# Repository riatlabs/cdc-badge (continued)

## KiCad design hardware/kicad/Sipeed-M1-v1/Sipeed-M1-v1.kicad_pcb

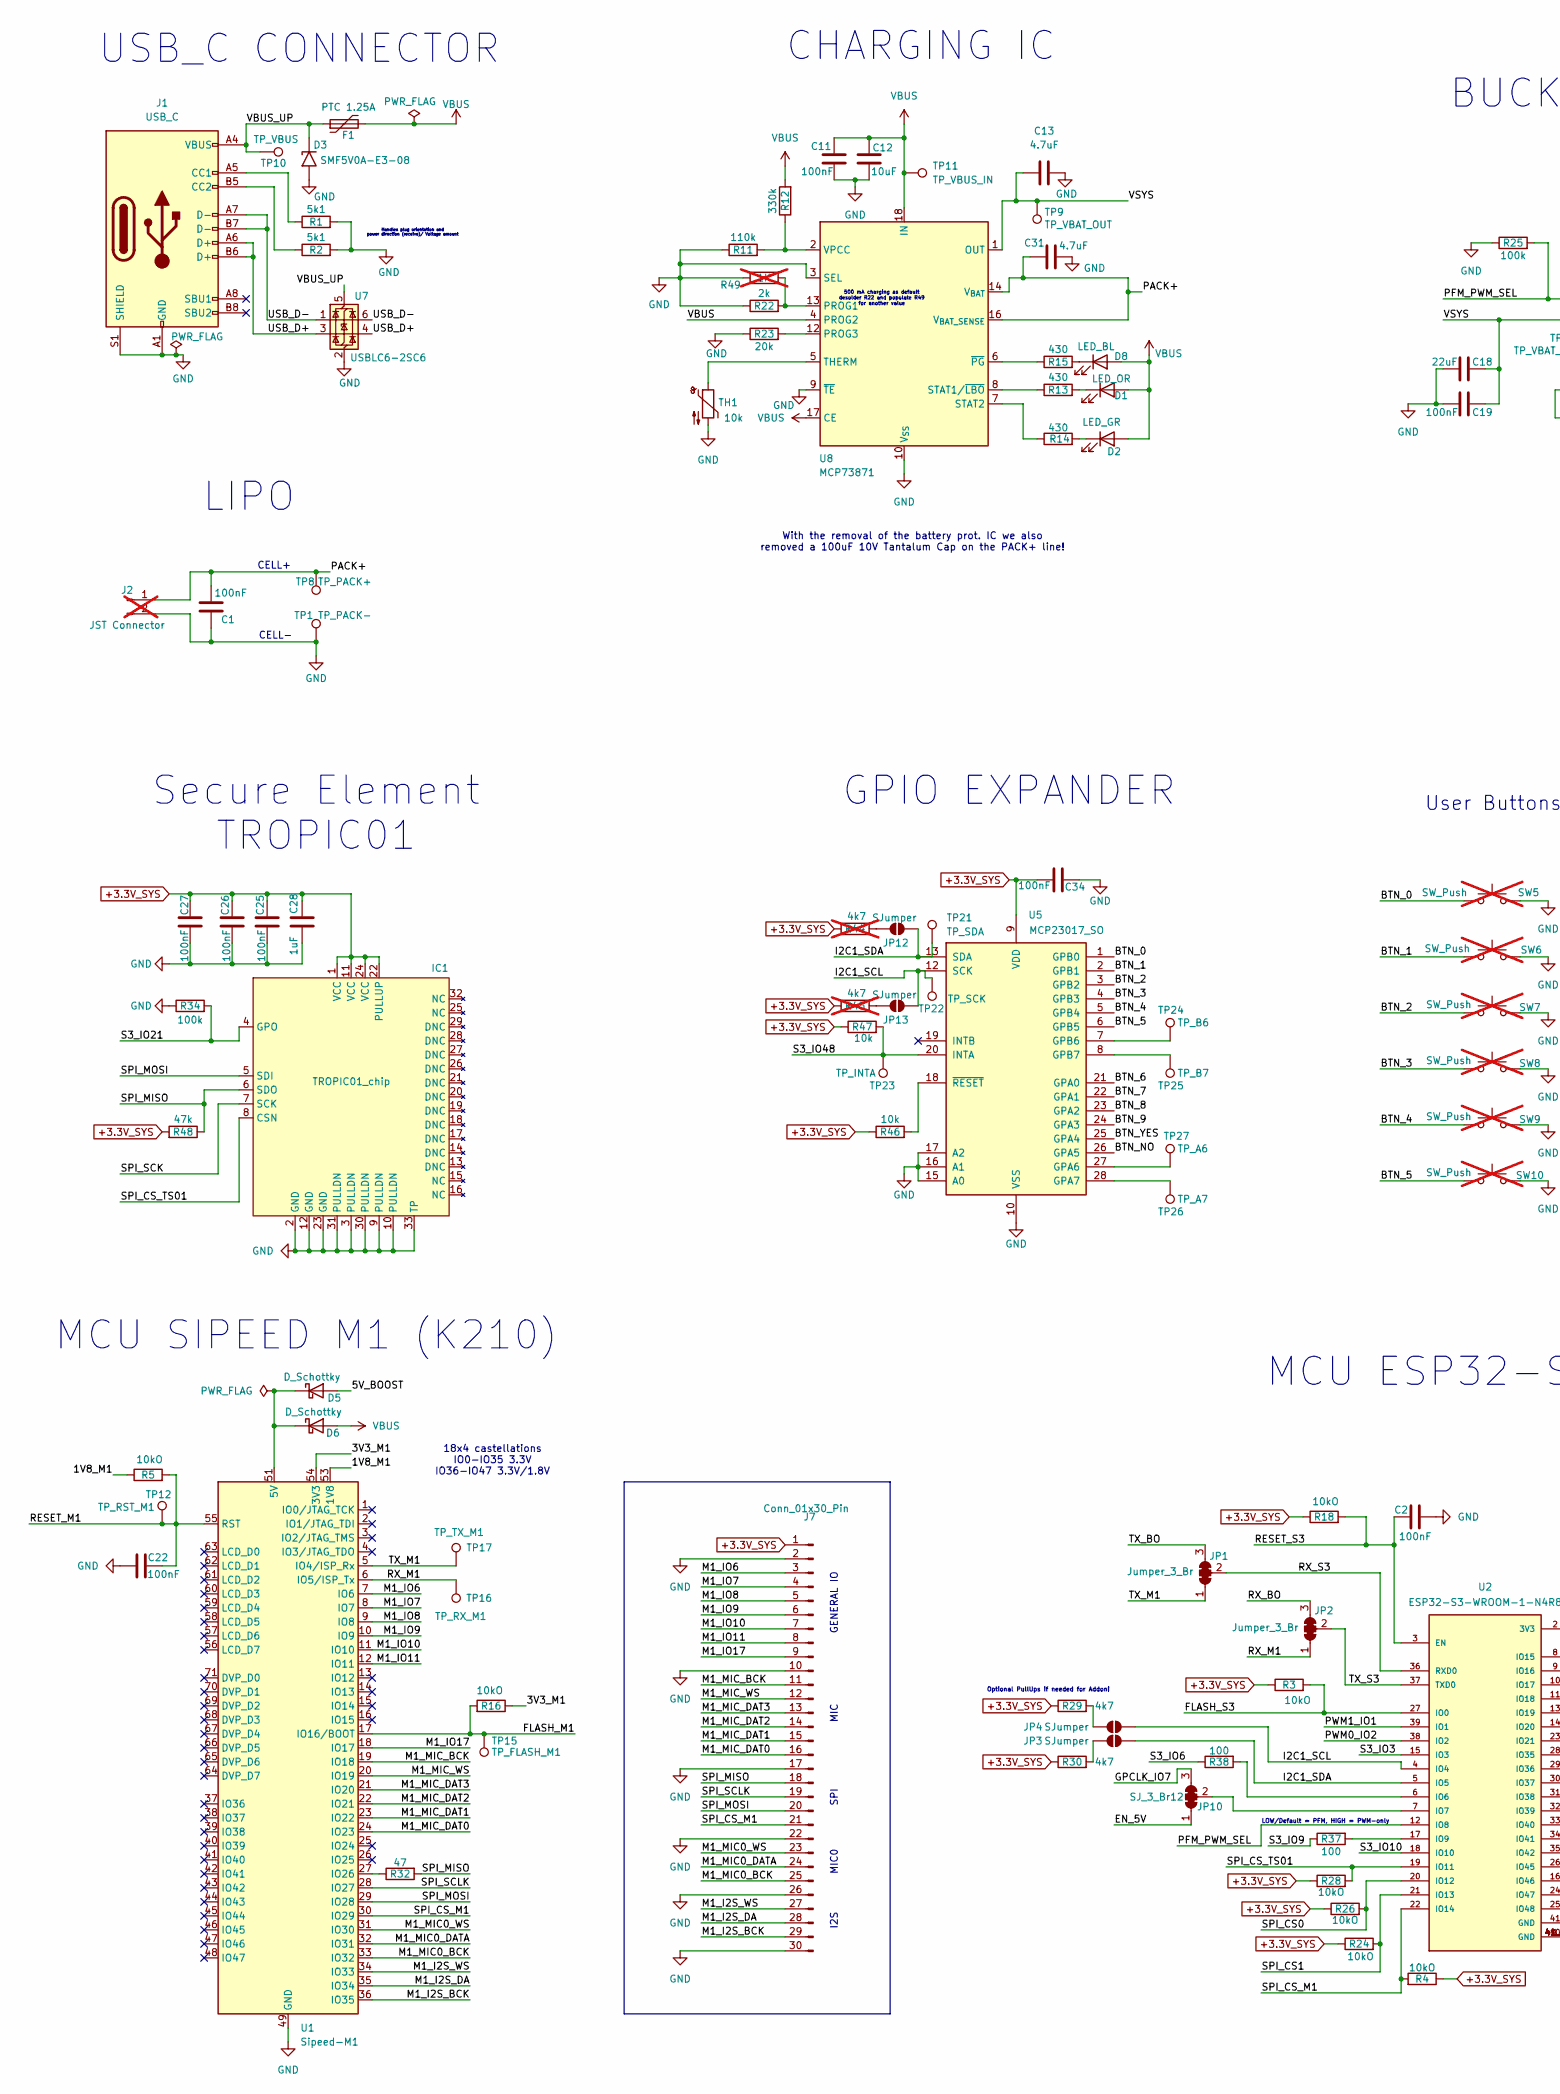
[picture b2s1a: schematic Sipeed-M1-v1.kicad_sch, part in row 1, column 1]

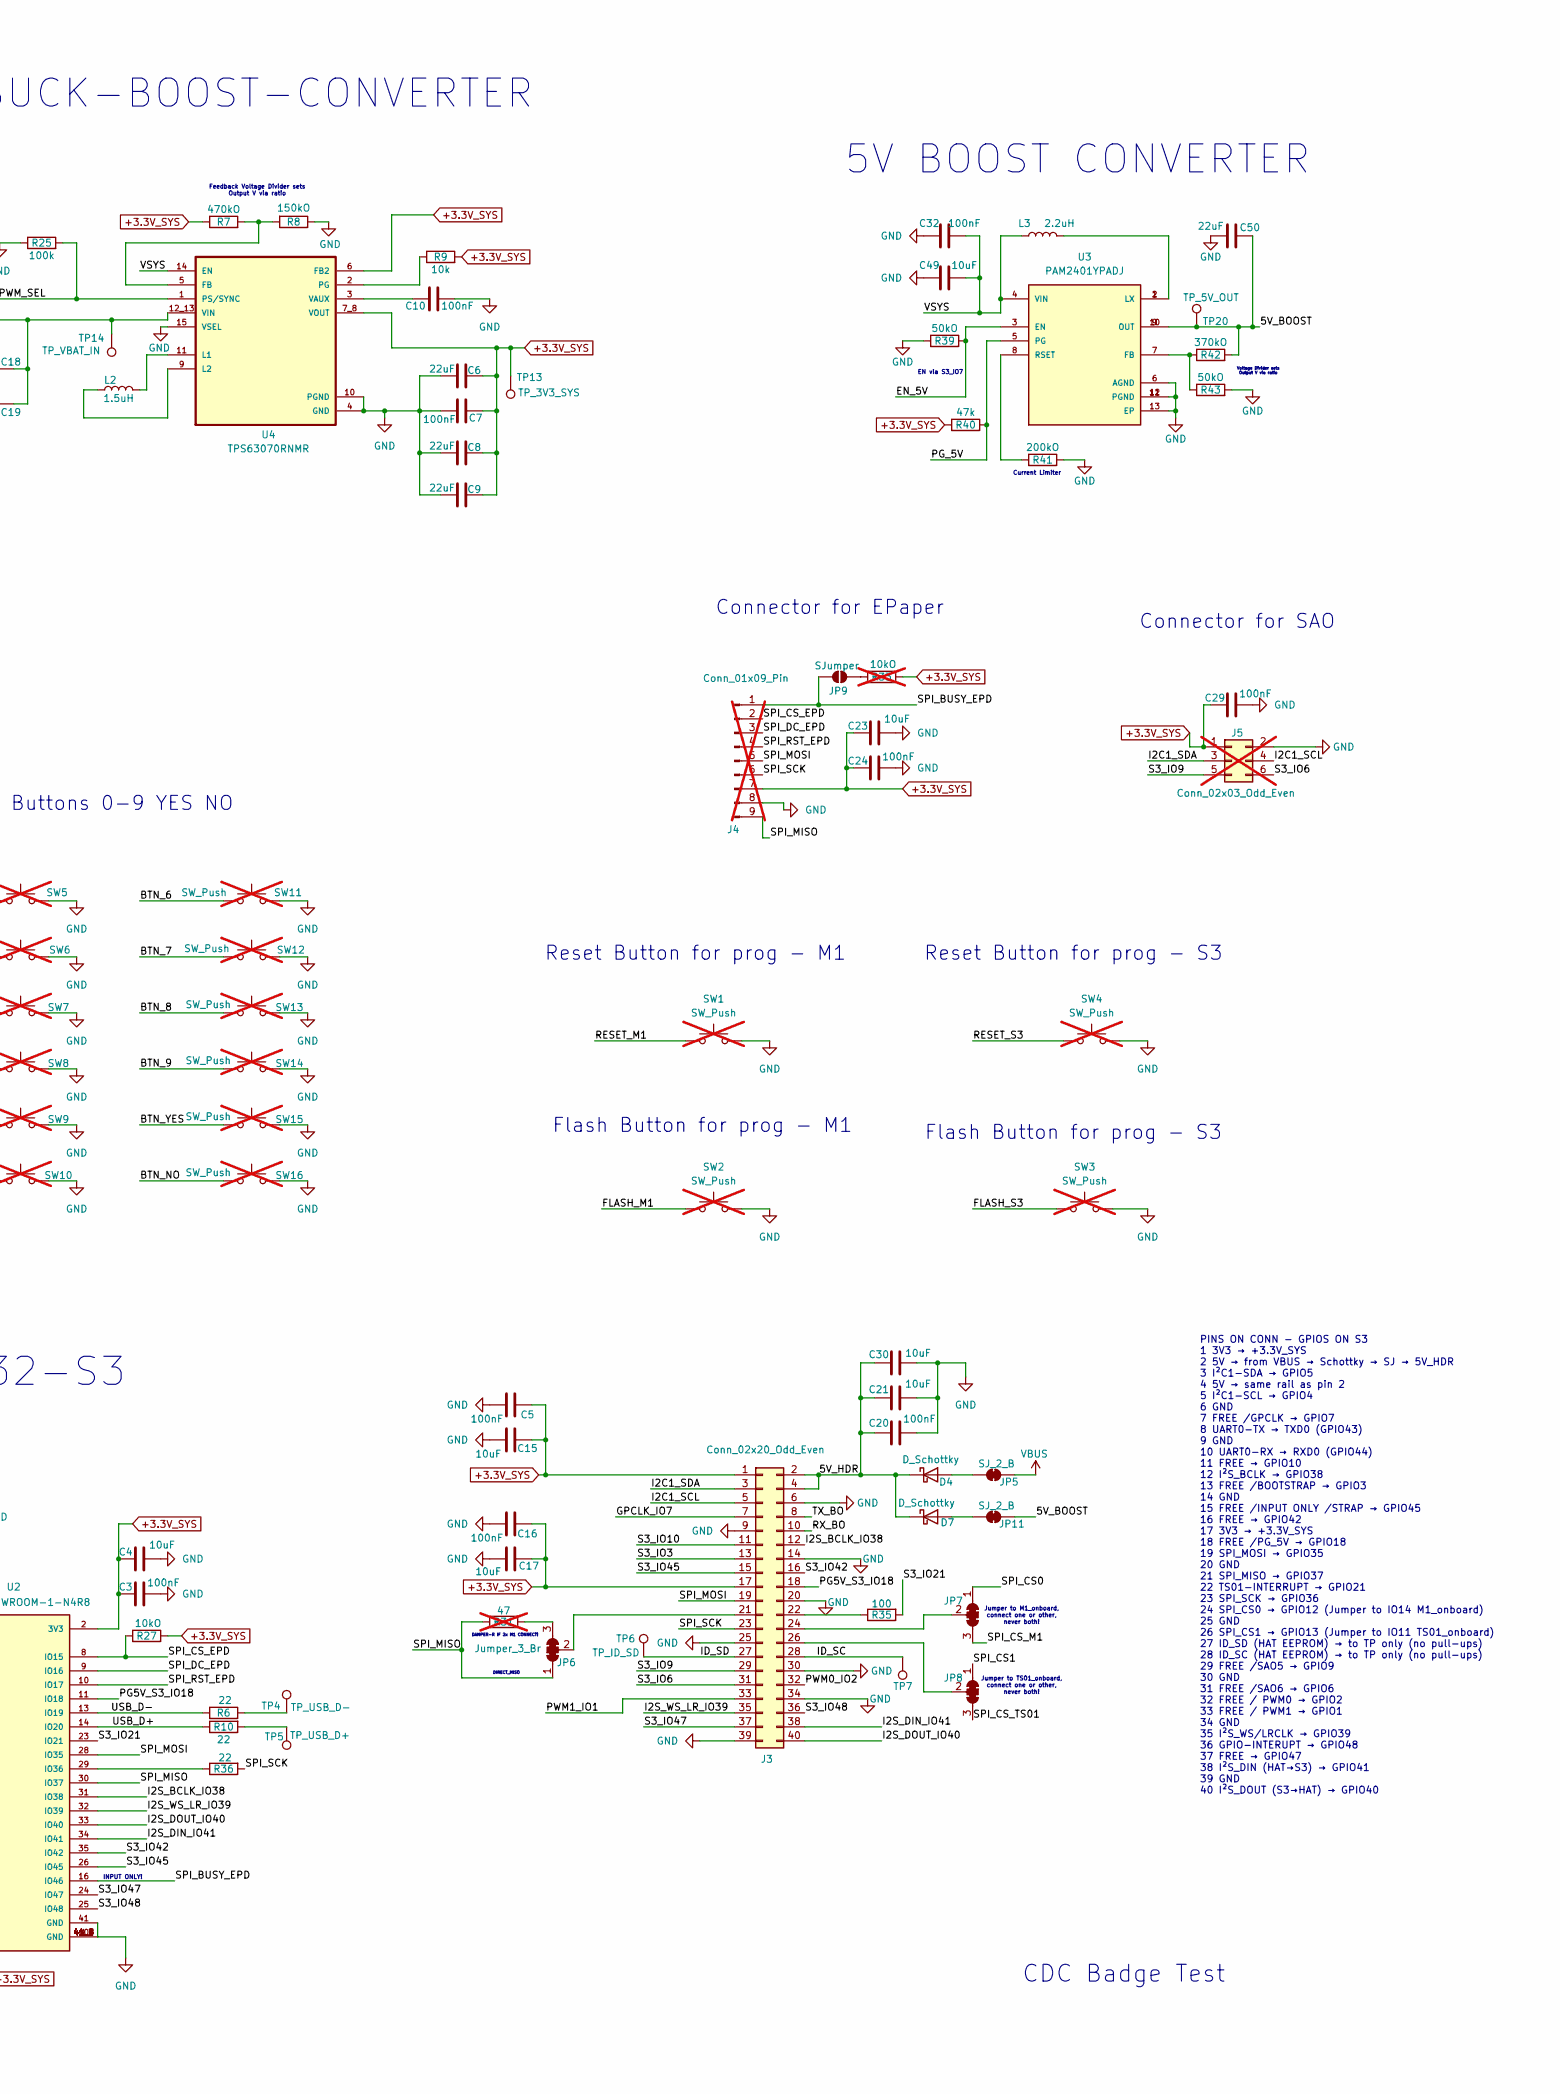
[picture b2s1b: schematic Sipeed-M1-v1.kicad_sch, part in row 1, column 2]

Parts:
C1, C2, C3, C5, C7, C10, C11, C16, C19, C20, C22, C24, C25, C26, C27, C29, C34: 100nF; C_0603_1608Metric
C4, C12, C15, C17, C21, C23, C30: 10uF; C_1206_3216Metric
C6, C8, C9, C18: 22uF; C_1206_3216Metric
C13, C31: 4.7uF; C_1206_3216Metric
C28: 1uF; C_0805_2012Metric
C32: 100nF; CP_EIA-3528-12_Kemet-T
C49: 10uF; CP_EIA-3528-12_Kemet-T
C50: 22uF; CP_EIA-3528-12_Kemet-T
D1: LED_OR; LED_0603_1608Metric
D2: LED_GR; LED_0603_1608Metric
D3: SMF5V0A-E3-08; D_SMF; JLCPCB PN C1972946
D4, D5, D6, D7: D_Schottky; D_SOD-123F
D8: LED_BL; LED_0603_1608Metric
F1: PTC 1.25A; Fuse_1812_4532Metric
IC1: TROPIC01_chip; TROPIC_QFN-32-1EP_4x4mm_P0.4mm_EP2.65x2.65mm
J1: USB_C; SHOUHAN_TYPE-C_16PIN_2MD__073_; JLCPCB PN C2765186
J2: JST Connector; JST_PH_S2B-PH-SM4-TB_1x02-1MP_P2.00mm_Horizontal; not fitted
J3: Conn_02x20_Odd_Even; PinHeader_2x20_P2.54mm_Vertical
J4: Conn_01x09_Pin; PinHeader_1x09_P2.54mm_Vertical; not fitted
J5: Conn_02x03_Odd_Even; PinSocket_2x03_P2.54mm_Vertical; not fitted
J7: Conn_01x30_Pin; PinHeader_1x30_P2.54mm_Vertical
JP1, JP2, JP6: Jumper_3_Br; SolderJumper-3_P1.3mm_Bridged12_RoundedPad1.0x1.5mm_NumberL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
JP3, JP4: SJumper; SolderJumper-2_P1.3mm_Bridged_RoundedPad1.0x1.5mm
JP5, JP11: SJ_2_B; SolderJumper-2_P1.3mm_Bridged_RoundedPad1.0x1.5mm
JP7, JP8: Jump_3_Br12; SolderJumper-3_P1.3mm_Bridged12_RoundedPad1.0x1.5mm_NumberL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
JP9, JP12, JP13: SJumper; SolderJumper-2_P1.3mm_Open_RoundedPad1.0x1.5mm
JP10: SJ_3_Br12; SolderJumper-3_P1.3mm_Bridged12_RoundedPad1.0x1.5mm_NumberL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
L2: 1.5uH; L_6.3x6.3_H3
L3: 2.2uH; L_6.3x6.3_H3
R1, R2: 5k1; R_0402_1005Metric
R3, R4, R5, R16, R18, R24, R26, R27, R28: 10kO; R_0603_1608Metric
R6, R10, R36: 22; R_0603_1608Metric
R7: 470kO; R_0805_2012Metric
R8: 150kO; R_0805_2012Metric
R9, R46, R47: 10k; R_0603_1608Metric
R11: 110k; R_0805_2012Metric
R12: 330k; R_0805_2012Metric
R13, R14, R15: 430; R_0603_1608Metric
R22: 2k; R_0603_1608Metric
R23: 20k; R_0603_1608Metric
R25: 100k; R_0805_2012Metric
R29, R30: 4k7; R_0603_1608Metric
R31: 47; R_Axial_DIN0207_L6.3mm_D2.5mm_P7.62mm_Horizontal; not fitted
R32: 47; R_0603_1608Metric
R33: 10kO; R_Axial_DIN0207_L6.3mm_D2.5mm_P7.62mm_Horizontal; not fitted
R34: 100k; R_0603_1608Metric
R35, R37, R38: 100; R_0603_1608Metric
R39, R43: 50kO; R_0603_1608Metric
R40, R48: 47k; R_0603_1608Metric
R41: 200kO; R_0805_2012Metric
R42: 370kO; R_0805_2012Metric
R44, R45: 4k7; R_Axial_DIN0207_L6.3mm_D2.5mm_P7.62mm_Horizontal; not fitted
R49: 1K; R_Axial_DIN0207_L6.3mm_D2.5mm_P7.62mm_Horizontal; not fitted
SW1, SW2, SW3, SW4, SW5, SW6, SW7, SW8, SW9, SW10, SW11, SW12, SW13, SW14, SW15, SW16: SW_Push; SW_PUSH_6mm_H5mm; not fitted
TH1: 10k; Fuse_1812_4532Metric
TP1: TP_PACK-; TestPoint_Pad_D2.0mm
TP4: TP_USB_D-; TestPoint_Pad_D2.0mm
TP5: TP_USB_D+; TestPoint_Pad_D2.0mm
TP6: TP_ID_SD; TestPoint_Pad_D2.0mm
TP7: TP_ID_SC; TestPoint_Pad_D2.0mm
TP8: TP_PACK+; TestPoint_Pad_D2.0mm
TP9: TP_VBAT_OUT; TestPoint_Pad_D2.0mm
TP10: TP_VBUS; TestPoint_Pad_D2.0mm
TP11: TP_VBUS_IN; TestPoint_Pad_D2.0mm
TP12: TP_RST_M1; TestPoint_Pad_D2.0mm
TP13: TP_3V3_SYS; TestPoint_Pad_D2.0mm
TP14: TP_VBAT_IN; TestPoint_Pad_D2.0mm
TP15: TP_FLASH_M1; TestPoint_Pad_D2.0mm
TP16: TP_RX_M1; TestPoint_Pad_D2.0mm
TP17: TP_TX_M1; TestPoint_Pad_D2.0mm
TP20: TP_5V_OUT; TestPoint_Pad_D2.0mm
TP21: TP_SDA; TestPoint_Pad_D2.0mm
TP22: TP_SCK; TestPoint_Pad_D2.0mm
TP23: TP_INTA; TestPoint_Pad_D2.0mm
TP24: TP_B6; TestPoint_Pad_D2.0mm
TP25: TP_B7; TestPoint_Pad_D2.0mm
TP26: TP_A7; TestPoint_Pad_D2.0mm
TP27: TP_A6; TestPoint_Pad_D2.0mm
U1: Sipeed-M1
U2: ESP32-S3-WROOM-1-N4R8; ESP32-S3-WROOM-1; PARTREV v1.1
U3: PAM2401YPADJ; PAM2401_SON45P300X300X63-13N; PARTREV 1-2
U4: TPS63070RNMR
U5: MCP23017_SO; SOIC-28W_7.5x17.9mm_P1.27mm
U7: USBLC6-2SC6; SOT-23-6; JLCPCB PN C7519
U8: MCP73871; QFN-20-1EP_4x4mm_P0.5mm_EP2.5x2.5mm

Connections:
+3.3V_SYS: C3.1, C4.1, C5.1, C6.2, C7.2, C8.2, C9.2, C15.1, C16.1, C17.1, C23.1, C24.1, C25.1, C26.1, C27.1, C28.1, C29.1, C34.2, IC1.1 (VCC), IC1.11 (VCC), IC1.22 (PULLUP), IC1.24 (VCC), J3.1, J3.17, J4.7, J5.1, J7.1, R3.1, R4.1, R7.1, R9.2, R18.1, R24.1, R26.1, R27.1, R28.1, R29.1, R30.1, R33.1, R40.2, R44.1, R45.1, R46.1, R47.1, R48.2, TP13.1, U2.2 (3V3), U4.6 (FB2), U4.7_8 (VOUT), U5.9 (VDD)
/1V8_M1: R5.1, U1.53 (1V8)
/3V3_M1: R16.1, U1.54 (3V3)
/5V_BOOST: C50.1, D5.2 (A), JP11.2 (B), R42.2, TP20.1, U3.9 (OUT), U3.10 (OUT)
/5V_HDR: C20.1, C21.1, C30.1, D4.1 (K), D7.1 (K), J3.2, J3.4
/BTN_0: SW5.1, U5.1 (GPB0)
/BTN_1: SW6.1, U5.2 (GPB1)
/BTN_2: SW7.1, U5.3 (GPB2)
/BTN_3: SW8.1, U5.4 (GPB3)
/BTN_4: SW9.1, U5.5 (GPB4)
/BTN_5: SW10.1, U5.6 (GPB5)
/BTN_6: SW11.1, U5.21 (GPA0)
/BTN_7: SW12.1, U5.22 (GPA1)
/BTN_8: SW13.1, U5.23 (GPA2)
/BTN_9: SW14.1, U5.24 (GPA3)
/BTN_NO: SW16.1, U5.26 (GPA5)
/BTN_YES: SW15.1, U5.25 (GPA4)
/EN_5V: JP10.1 (A), R39.1, U3.3 (EN)
/FLASH_M1: R16.2, SW2.1, TP15.1, U1.17 (IO16/BOOT)
/FLASH_S3: R3.2, SW3.1, U2.27 (IO0)
/GPCLK_IO7: J3.7, JP10.3 (B)
/I2C1_SCL: J3.5, J5.4, JP4.2 (B), JP13.2 (B), TP22.1, U2.4 (IO4), U5.12 (SCK)
/I2C1_SDA: J3.3, J5.3, JP3.2 (B), JP12.2 (B), TP21.1, U2.5 (IO5), U5.13 (SDA)
/I2S_BCLK_IO38: J3.12, U2.31 (IO38)
/I2S_DIN_IO41: J3.38, U2.34 (IO41)
/I2S_DOUT_IO40: J3.40, U2.33 (IO40)
/I2S_WS_LR_IO39: J3.35, U2.32 (IO39)
/ID_SC: J3.28, TP7.1
/ID_SD: J3.27, TP6.1
/M1_I2S_BCK: J7.29, U1.36 (IO35)
/M1_I2S_DA: J7.28, U1.35 (IO34)
/M1_I2S_WS: J7.27, U1.34 (IO33)
/M1_IO6: J7.3, U1.7 (IO6)
/M1_IO7: J7.4, U1.8 (IO7)
/M1_IO8: J7.5, U1.9 (IO8)
/M1_IO9: J7.6, U1.10 (IO9)
/M1_IO10: J7.7, U1.11 (IO10)
/M1_IO11: J7.8, U1.12 (IO11)
/M1_IO17: J7.9, U1.18 (IO17)
/M1_MIC0_BCK: J7.25, U1.33 (IO32)
/M1_MIC0_DATA: J7.24, U1.32 (IO31)
/M1_MIC0_WS: J7.23, U1.31 (IO30)
/M1_MIC_BCK: J7.11, U1.19 (IO18)
/M1_MIC_DAT0: J7.16, U1.24 (IO23)
/M1_MIC_DAT1: J7.15, U1.23 (IO22)
/M1_MIC_DAT2: J7.14, U1.22 (IO21)
/M1_MIC_DAT3: J7.13, U1.21 (IO20)
/M1_MIC_WS: J7.12, U1.20 (IO19)
/PACK+: C1.2, C31.1, J2.1, TP8.1, U8.14 (V_{BAT}), U8.15 (V_{BAT}), U8.16 (V_{BAT_SENSE})
/PFM_PWM_SEL: R25.2, U2.12 (IO8), U4.1 (PS/SYNC)
/PG5V_S3_IO18: J3.18, U2.11 (IO18)
/PG_5V: R40.1, U3.5 (PG)
/PWM0_IO2: J3.32, U2.38 (IO2)
/PWM1_IO1: J3.33, U2.39 (IO1)
/RESET_M1: C22.1, R5.2, SW1.1, TP12.1, U1.55 (RST)
/RESET_S3: C2.1, R18.2, SW4.1, U2.3 (EN)
/RX_BO: J3.10, JP2.3 (B)
/RX_M1: JP2.1 (A), TP16.1, U1.6 (IO5/ISP_Tx)
/RX_S3: JP1.2 (C), U2.36 (RXD0)
/S3_IO3: J3.13, U2.15 (IO3)
/S3_IO6: J3.31, J5.6, R38.1
/S3_IO9: J3.29, J5.5, R37.1
/S3_IO10: J3.11, U2.18 (IO10)
/S3_IO21: IC1.4 (GPO), R34.2, R35.2, U2.23 (IO21)
/S3_IO42: J3.16, U2.35 (IO42)
/S3_IO45: J3.15, U2.26 (IO45)
/S3_IO47: J3.37, U2.24 (IO47)
/S3_IO48: J3.36, R47.2, TP23.1, U2.25 (IO48), U5.20 (INTA)
/SPI_BUSY_EPD: J4.1, JP9.1 (A), U2.16 (IO46)
/SPI_CS0: JP7.1 (A), R26.2, U2.20 (IO12)
/SPI_CS1: JP8.1 (A), R24.2, U2.21 (IO13)
/SPI_CS_EPD: J4.2, R27.2, U2.8 (IO15)
/SPI_CS_M1: J7.21, JP7.3 (B), R4.2, U1.30 (IO29), U2.22 (IO14)
/SPI_CS_TS01: IC1.8 (CSN), JP8.3 (B), R28.2, U2.19 (IO11)
/SPI_DC_EPD: J4.3, U2.9 (IO16)
/SPI_MISO: IC1.6 (SDO), J4.9, J7.18, JP6.1 (A), R31.1, R32.2, R48.1, U2.30 (IO37)
/SPI_MOSI: IC1.5 (SDI), J3.19, J4.5, J7.20, U1.29 (IO28), U2.28 (IO35)
/SPI_RST_EPD: J4.4, U2.10 (IO17)
/SPI_SCK: IC1.7 (SCK), J3.23, J4.6, R36.2
/SPI_SCLK: J7.19, U1.28 (IO27)
/TX_BO: J3.8, JP1.3 (B)
/TX_M1: JP1.1 (A), TP17.1, U1.5 (IO4/ISP_Rx)
/TX_S3: JP2.2 (C), U2.37 (TXD0)
/USB_D+: J1.A6 (D+), J1.B6 (D+), R10.1, U2.14 (IO20), U7.3 (I/O2), U7.4 (I/O2)
/USB_D-: J1.A7 (D-), J1.B7 (D-), R6.2, U2.13 (IO19), U7.1 (I/O1), U7.6 (I/O1)
/VBUS_UP: D3.1 (A1), F1.1, J1.A4 (VBUS), J1.A9 (VBUS), J1.B4 (VBUS), J1.B9 (VBUS), TP10.1, U7.5 (VBUS)
/VSYS: C13.1, C18.2, C19.2, C32.1, C49.1, L3.1, TP9.1, TP14.1, U3.4 (VIN), U4.12_13 (VIN), U4.14 (EN), U8.1 (OUT), U8.20 (OUT)
GND: C1.1, C2.2, C3.2, C4.2, C5.2, C6.1, C7.1, C8.1, C9.1, C10.1, C11.2, C12.1, C13.2, C15.2, C16.2, C17.2, C18.1, C19.1, C20.2, C21.2, C22.2, C23.2, C24.2, C25.2, C26.2, C27.2, C28.2, C29.2, C30.2, C31.2, C32.2, C34.1, C49.2, C50.2, D3.2 (A2), IC1.2 (GND), IC1.3 (PULLDN), IC1.9 (PULLDN), IC1.10 (PULLDN), IC1.12 (GND), IC1.23 (GND), IC1.30 (PULLDN), IC1.31 (PULLDN), IC1.33 (TP), J1.A1 (GND), J1.A12 (GND), J1.B1 (GND), J1.B12 (GND), J1.S1 (SHIELD), J2.2, J3.6, J3.9, J3.14, J3.20, J3.25, J3.30, J3.34, J3.39, J4.8, J5.2, J7.2, J7.10, J7.17, J7.22, J7.26, J7.30, R1.2, R2.2, R8.1, R11.1, R22.1, R23.1, R25.1, R34.1, R39.2, R41.1, R43.2, R49.1, SW1.2, SW2.2, SW3.2, SW4.2, SW5.2, SW6.2, SW7.2, SW8.2, SW9.2, SW10.2, SW11.2, SW12.2, SW13.2, SW14.2, SW15.2, SW16.2, TH1.2, TP1.1, U1.49 (GND), U1.50 (GND), U1.72 (GND), U2.1 (GND), U2.40 (GND), U2.41 (GND), U2.41_1 (GND), U2.41_2 (GND), U2.41_3 (GND), U2.41_4 (GND), U2.41_5 (GND), U2.41_6 (GND), U2.41_7 (GND), U2.41_8 (GND), U2.41_9 (GND), U3.6 (AGND), U3.11 (PGND), U3.12 (PGND), U3.13 (EP), U4.4 (GND), U4.10 (PGND), U4.15 (VSEL), U5.10 (VSS), U5.15 (A0), U5.16 (A1), U5.17 (A2), U7.2 (GND), U8.3 (SEL), U8.9 (~TE), U8.10 (V_{SS}), U8.11 (V_{SS}), U8.21 (V_{SS})
unnamed: D1.1 (K), R13.2
unnamed: D2.1 (K), R14.2
unnamed: D4.2 (A), JP5.1 (A)
unnamed: D5.1 (K), D6.1 (K), U1.51 (5V), U1.52 (5V)
unnamed: D7.2 (A), JP11.1 (A)
unnamed: D8.1 (K), R15.2
unnamed: J1.A5 (CC1), R1.1
unnamed: J1.B5 (CC2), R2.1
unnamed: J3.21, JP6.2 (C)
unnamed: J3.22, R35.1
unnamed: J3.24, JP7.2 (C)
unnamed: J3.26, JP8.2 (C)
unnamed: JP3.1 (A), R30.2
unnamed: JP4.1 (A), R29.2
unnamed: JP6.3 (B), R31.2
unnamed: JP9.2 (B), R33.2
unnamed: JP10.2 (C), U2.7 (IO7)
unnamed: JP12.1 (A), R44.2
unnamed: JP13.1 (A), R45.2
unnamed: L3.2, U3.1 (LX), U3.2 (LX)
unnamed: R6.1, TP4.1
unnamed: R10.2, TP5.1
unnamed: R32.1, U1.27 (IO26)
unnamed: R38.2, U2.6 (IO6)
unnamed: R37.2, U2.17 (IO9)
unnamed: R36.1, U2.29 (IO36)
unnamed: R42.1, R43.1, U3.7 (FB)
unnamed: R41.2, U3.8 (RSET)
unnamed: R7.2, R8.2, U4.5 (FB)
unnamed: L2.2, U4.11 (L1)
unnamed: L2.1, U4.9 (L2)
unnamed: R9.1, U4.2 (PG)
unnamed: C10.2, U4.3 (VAUX)
unnamed: TP27.1, U5.27 (GPA6)
unnamed: TP26.1, U5.28 (GPA7)
unnamed: TP24.1, U5.7 (GPB6)
unnamed: TP25.1, U5.8 (GPB7)
unnamed: R46.2, U5.18 (~RESET)
unnamed: R22.2, R49.2, U8.13 (PROG1)
unnamed: R23.2, U8.12 (PROG3)
unnamed: R13.1, U8.8 (STAT1/~LBO)
unnamed: R14.1, U8.7 (STAT2)
unnamed: TH1.1, U8.5 (THERM)
unnamed: R11.2, R12.1, U8.2 (VPCC)
unnamed 134: R15.1, U8.6 (~PG); also elsewhere on the board
VBUS: C11.1, C12.2, D1.2 (A), D2.2 (A), D6.2 (A), D8.2 (A), F1.2, JP5.2 (B), R12.2, TP11.1, U8.4 (PROG2), U8.17 (CE), U8.18 (IN), U8.19 (IN); also elsewhere on the board

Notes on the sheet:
MCU ESP32-S3
User Buttons 0-9 YES NO
18x4 castellations IO0-IO35 3.3V IO36-IO47 3.3V/1.8V
BUCK-BOOST-CONVERTER
GENERAL IO
LIPO
MIC0
CELL-
Handles plug orientation and power direction (receive)/ Voltage amount
EN via S3_IO7
USB_C CONNECTOR
Connector for EPaper
Jumper to M1_onboard, connect one or other, never both!
Reset Button for prog - S3
CDC Badge Test
LOW/Default = PFM, HIGH = PWM-only
MIC
Reset Button for prog - M1
GPIO EXPANDER
Jumper to TS01_onboard, connect one or other, never both!
I2S
500 mA charging as default desolder R22 and populate R49 for another value
MCU SIPEED M1 (K210)
Flash Button for prog - S3
INPUT ONLY!
SPI
Optional PullUps if needed for Addon!
Secure Element TROPIC01
Voltage Divider sets Output V via ratio
DAMPER-R IF 2x M1 CONNECT!
Current Limiter
5V BOOST CONVERTER
PINS ON CONN - GPIOS ON S3 1 3V3 → +3.3V_SYS 2 5V → from VBUS → Schottky → SJ → 5V_HDR 3 I²C1-SDA → GPIO5 4 5V → same rail as pin 2 5 I²C1-SCL → GPIO4 6 GND 7 FREE /GPCLK → GPIO7 8 UART0-TX → TXD0 (GPIO43) 9 GND 10 UART0-RX → RXD0 (GPIO44) 11 FREE → GPIO10 12 I²S_BCLK → GPIO38 13 FREE /BOOTSTRAP → 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
CELL+
Connector for SAO
With the removal of the battery prot. IC we also removed a 100uF 10V Tantalum Cap on the PACK+ line!
Flash Button for prog - M1
DIRECT_MISO
CHARGING IC
Feedback Voltage Divider sets Output V via ratio

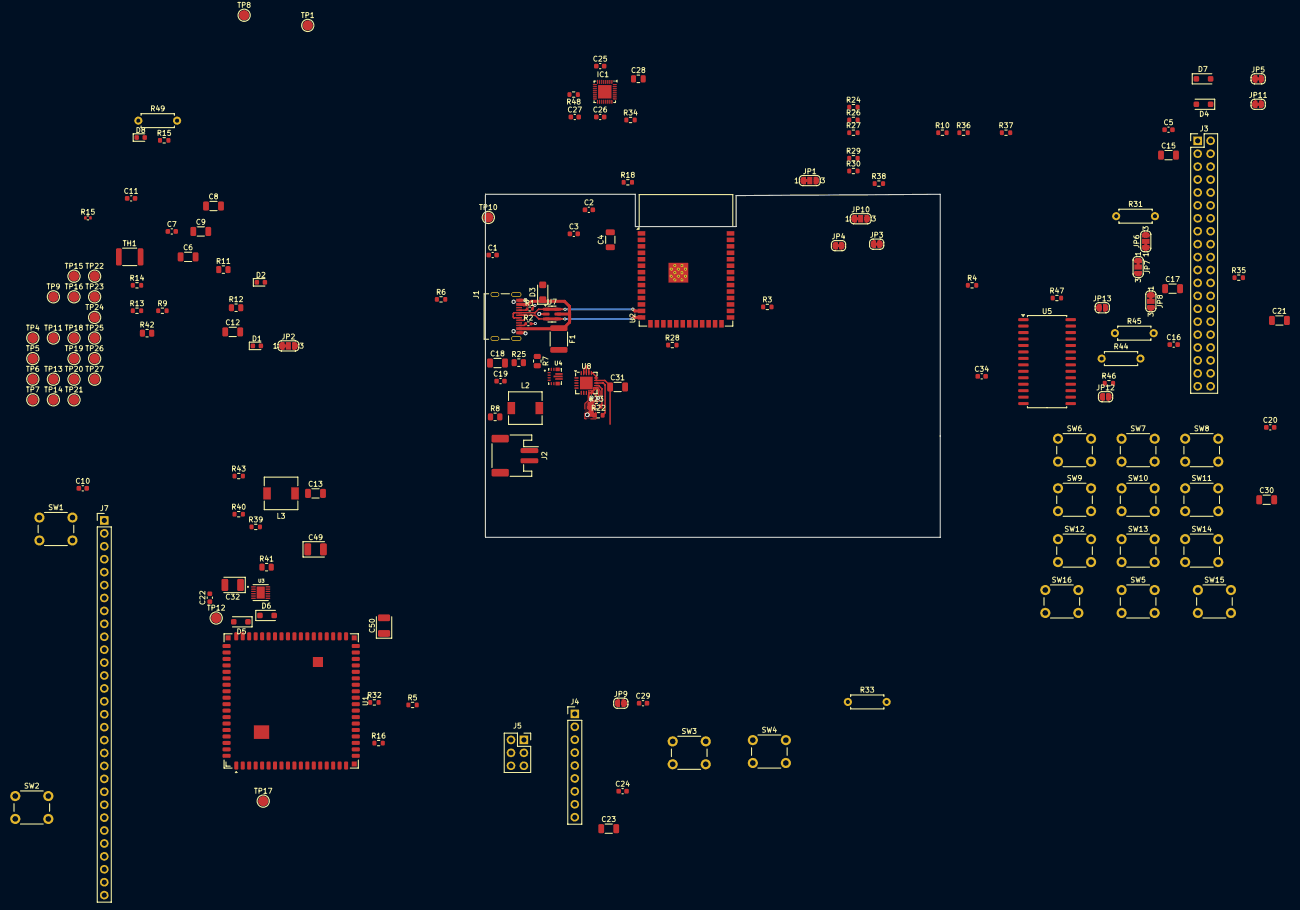
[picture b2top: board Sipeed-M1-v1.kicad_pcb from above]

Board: 2 copper layers, 89.4 x 67.4 mm, 160 parts (0 on the bottom side), 134 nets.

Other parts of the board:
R15#2: 10k; R_0402_1005Metric
TP18: TP_ISP_RX_M1; TestPoint_Pad_D2.0mm
TP19: TP_ISP_TX_M1; TestPoint_Pad_D2.0mm

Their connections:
unnamed 134: R15#2.1; also elsewhere on the board
VBUS: R15#2.2; also elsewhere on the board

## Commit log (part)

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2025-09-04 added kicad file and hardwarenotes (migrated from old repo)
2025-09-06 added raspi-scheme breakout and multiple wiring
2025-09-07 added GPIO extender and sorted pcb layout
2025-09-09 cleared some errors for pcb import from schematic(update pcb)
2025-09-11 adding M1 changes
2025-09-11 adding todo
2025-09-11 tiny layout fixes
2025-09-12 Added the footprint folder to the project
2025-09-13 updated pcb, added 3v3 and 1v8 net to m1, checked proper deletion of battery prot IC as lipos have their own
2025-09-16 USB-C connector now using SHOU HAN TYPE-C 16PIN 2MD(073)
    Adding footprint and 3D model.
2025-09-16 ESD protection diode: opt for 5V version
    Adding JLCPC PN
2025-09-17 New FPs for ESP32-S3, R1 and R2. Initial PCB routing.
    Opted for ESP32-S3 with embedded PCB antenna.
    R1 and R2 are now smaller to fit next to USB-C connector.
2025-09-18 Add license, copyright and changelog.
    Changelog should follow Common Changelog https://common-changelog.org
2025-09-18 refactor: remove unused symbols
2025-10-02 Add authorship and licenses of 3rd party resources
2025-10-09 docs: choose power sub-system chips
2025-10-09 schematic: USB-C connector peripherals revamp
    Remove PTC. Charging IC has over current protection.
    Add ESD protection to CC lines.
    Add JLCPCB part numbers to resistors.
    Increase resistors size to 0603 (1608m).
2025-10-11 docs: LiPo voltage ranges and relationship with buck converter
2025-10-12 schematic: connect PMID and ILIM pins on charging IC
2025-10-12 schematic: remove optional 5V sources for M1 and header
    The BQ25895 is able to supply VSYS even when no battery is connected.
    No more need to have the option between VBUS and +5V to power the M1 and
    the Rasp Pi header. The boost converter will always output +5V.
2025-10-12 schematic: remove power flags, fix power pin type in symbols
2025-10-13 schematic: replace 3.3V boost-buck for a simple buck
    Possible because BQ25895 charging IC keeps VSYS over 3.3V.
    Makes things cheaper and simple.
    Document inductor selection.
    Add skeleton of Python script that would calculate the feed forward
    capacitor. Abandoned as we have no proper way to determine the crossover
    frequency.
2025-10-13 schematic: replace 5V boost converter
    Now using the TPS613222A which is a fixed voltage converter and thus
    more simple to use and requiring less passive components.
    It is also cheaper and more available than the PAM2401.
2025-10-14 Move Sipeed M1 to it's own repository.
2025-10-14 schematic: remove bulk capacitors from GPIO header
    The Raspberry Pi does not have them. That's responsibility of the HAT.
2025-10-20 schematic: populate Rasp Pi and SAO headers
2025-10-22 schematic: add debouncing and separate keypad
    Document debouncing approach.
2025-10-22 schematic: add LED driver for the e-paper backlight
    Document the design choices.
2025-10-23 schematic: input DSEL to MCU, label multi-function buttons
2025-10-25 Add symbols and footprints for battery and display
    With these it's easier to reserve space for them in the PCB.
    Finish RPi header wiring.
2025-10-25 docs: clarify 3rd party resources' authorship
2025-10-26 schematic: test points, remove not needed, add for USB data
    Add ferrite beads to USB power lines to keep EMI out of the cable,
    as per Texas Instruments SPRAAR7A application report.
2025-10-27 schematic: ceetee reviews, e-paper display
    Add pull-up on chip select.
2025-10-27 Add mounting holes: HAT format and lanyard.
2025-10-28 schematic: fix frontlight connector orientation
    The Jushuo connector we are using has its pins numbered in the reverse
    order of the frontlight connector shown on the GDEY029T94-FL03
    datasheet.
2025-10-28 schematic: ceetee reviews, add power output decoupling capacitors
2025-10-29 schematic: ceetee reviews, add pull-ups to all SPI CS
2025-10-29 pcb: relax ESP32 keep-out zone, import from schematic
2025-10-30 schematic: ceetee reviews, Grove connector
    Add selectable output voltage with a switch.
    Add optional pull-ups for I2C.
2025-10-30 schematic: ceetee reviews, buck converter
    Use more common resistor values in the voltage divider.
    Add optional feed forward capacitor.
2025-10-30 PCB. Schem: changed TP to smaller FP
2025-10-30 schematic: ceetee reviews, charging IC
    Lower status LED current and connect to stable voltage source.
    Use standard values for config resistors.
    Add pull-downs to OTG and CE to allow hacking.
    Warn about need to set max charge current in firmware.
2025-10-31 docs: update 3rd party resources
2025-10-31 Schem: Removed TP 3V 5V, PCB: Switched Grove FP to hor., rewiring
2025-10-31 schematic: fix Vbus test point location
2025-10-31 PCB: replaced TP for VBUS and Grove switch
2025-10-31 PCB: Reviewed wirings, fixed some errors
2025-11-01 DRU : change dsign rules to make edge clearance from 0.2 to 0.3mm
2025-11-01 footprints: add 3D models for diodes
2025-11-02 schematic: ceetee reviews, remove ferrite bead from GND
    "In most cases the ferrite bead will not have any measurable effect.
    In some it makes it worse, and in very few it is helpful."
    -- ceetee
2025-11-02 schematic: ceetee reviews, Grove voltage selector
    Use solder jumper instead of switch. Switch could lead to accidental
    burning of add-ons. There are very few using 5V exclusively anyway.
2025-11-02 schematic: ceetee reviews, e-paper display power converter
    Relocate negative voltage output capacitor for better readability.
2025-11-02 PCB: Align critical parts to grid and lock them there
2025-11-03 PCB: Placing the connectors, display and battery and lock them
2025-11-03 PCB: USB-C, Datatracks and Charging IC placement draft
2025-11-03 PCB: 3V3 area pour on front and back, GND pour on inner layers. Area prio adjust
2025-11-03 pcb: layout boost converter, review charging IC zones
2025-11-04 PCB: Routing the tracks from charging IC
2025-11-04 PCB: Finished component placement for Charging IC
2025-11-05 docs: acknowledge ceetee
2025-11-05 PCB: move some other vias and tracks at USB-conn to resolve EDC errors
2025-11-05 PCB: placed pullups for I2C0 dataline
2025-11-05 PCB: adjusted graphics and text width values
    We used text and line width minimum 0.15mm, manufacturer capability is 0.153mm (6mil) min.
    -adjusted default min width for text and graphics accordingly in board setup
    -adjusted all existing widths in project to manufacturer minimum
2025-11-06 PCB: place caps to 3.3v and 5v pins at raspi conn.
2025-11-07 PCB: route SPI connections and others
2025-11-07 rerouting of several connections between s3 and raspi conn.
2025-11-08 routing the buttons
2025-11-09 PCB: rerouting and replacement
    -rerouting of bat+ track to clear area round raspi-header mounthole
    -rerouting of the SPI connection to optimize routes
    -moving the 5V system 1mm away from charging IC to separate inductors
2025-11-09 Edge-Track clearance increased, glitch resistor edited
    -Custom Rules: increased edge-to-track clearance to min. 0.5mm
    -Schem: set R41 (tropic01 glitching location) to DNP and connect
    the path (to be scratched there)
    -Schem: relink inverted (flipped) battery FP to battery symbol
    -PCB: updated the pcb from schem, including bat FP
2025-11-10 schematic: change test points footprint
    Now using a plated hole instead of a pad. Makes it easier to probe with
    a multimeter.
2025-11-10 docs: explain bottom entry SAO port choice
2025-11-11 placed TP's, SAO and grove labels and GND vias on MP edges
2025-11-11 minor changes to accomomdate the secondary labels below the buttons
2025-11-12 schematic, footprint: add keep out zone to Rasp Pi mounting holes
2025-11-12 schematic, docs: inform about deep sleep power consumption
2025-11-12 docs: move info from design choices to README
2025-11-12 docs, schematic: link to datasheets
2025-11-12 docs: fix formatting of datasheets doc
2025-11-13 small changes to the mesh graphic
2025-11-13 Add MPN to all symbols.
    Makes BOM ready for other manufacturers besides JLCPCB.
2025-11-13 setup exports, remove unpopulated from BOM
2025-11-13 pcb: repour after changing GND pads vias
2025-11-14 schematic: fix, battery connector was not in BOM
2025-11-14 pcb: fix silkscreen
    Make sure silkscreen is not on top of vias.
    Show missing designators.
2025-11-14 pcb: center tracks in Rasp Pi connector with imperial grid
2025-11-14 pcb: fix stackup layer thicknesses
    According to JLC04161H-7628 stackup.
    https://jlcpcb.com/impedance
    Use ENIG as copper finish for some nice PCB art in the future.
2025-11-14 pcb: fix footprint related DRC warnings
2025-11-16 Script to panelize PCB using KiKit.
    Usage instructions in README.
2025-11-18 trying out to create a mesh network graphic with exposed gold
2025-11-20 repositioned labels: CSO, C37, C1, R12, L1
2025-11-23 docs: remove mention to custom Sipeed M1 HAT
    Will be developed only for 40C3. The Grove AI HAT for Edge Computing can
    be used in the meantime.
2025-11-23 pcb: move 3.3V via away from edge
2025-11-23 pcb: remove redundant check from custom DRCs rules
    Minimum track width is already set in the project configs.
2025-11-24 pcb: increase general clearance to 0.127 mm (5 mil)
    Makes PCB cheaper to produce in multiple fabs.
2025-11-24 schematic: add mounting pins to battery connector
    Fixes liking with PCB.
    Remove non-generic fields from symbols.
2025-11-24 Relax NextPCB DRC rules
    Better alignment with JLCPCB.
2025-11-27 footprints: fix SOD-123FL, add datasheets to descriptions
2025-11-29 footprints: move datasheet link from field to description
2025-12-08 pcb: add proper reference to OSHW logo
2025-12-09 pcb: move Grove connector 1mm to the left
2025-12-09 pcb: enlarge flex cable cut-out by 3mm down
2025-12-09 Do not populate SAO but add pads for it on both sides.
    The HC-PM254-8.5H-2x3PS part does not work for bottom entry.
    Opting to leave the pads unpopulated and solder the 610006243021 from
    Würth Elektronik by hand.
2025-12-10 docs: move firmware instructions into their own doc
    Elaborate on what each firmware must implement in order to operate
    safely.
2025-12-10 pcb: add more ground vias near signal vias
2025-12-10 pcb fix: kikit fabrication output cannot handle multiline knockouts
2026-01-09 Move case to it's own directory. Add README.
2026-01-11 cases: add Ari's case and improve descriptions
2026-01-11 cases: arrange into directories
2026-01-11 pcb: new OSHW logo filled with a mesh network
    Reposition TROPIC01 resistors and caps to match the nodes.
2026-01-31 docs: README, link to firmwares, put them up
2026-02-12 Update README.md
    changed broken ALPS button data sheet link to product page of buttons
2026-02-13 cases: Rasp Pi header cap by bobotronic
2026-02-15 cases: add photos of ct's case to README
